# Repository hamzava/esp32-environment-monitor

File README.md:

# 🌱 ESP32 Environment Monitoring System
### Using ESP32 + ESP-IDF + I2C Sensors

🟢 This project represents an exploration into embedded firmware architecture, multi layer hardware design, and communication protocol integration using the ESP32 platform and the ESP-IDF framework.

## ◆ Project Overview

🟥 This project is a Environment Monitor prototype built using:

 - ESP-32 & ESP-IDF
 - BME280 Atmosphere Sensor
 - LTR390 UV Sensor

🟥 The objective was to to acquire environmental data from digital sensors and prepare it for network-based transmission.

This prototype is focused on:

✔ Multi-layer PCB & hardware design  </br>
✔ ESP-IDF firmware development </br>
✔ Peripheral communication via I2C </br>
✔ Power supply and regulation </br>

## ◆ Current Status:
- Fully operational Embedded System from working 4 layer PCB to a running ESP-IDF Super Loop

## ◆ Project Aims & Development Roadmap <br />
- This project was structured around incremental, demonstrable milestones, rather than a single monolithic goal.

## ✅ Completed / Implemented: 
🟢 Completely Functional 4-Layer PCB <br />
🟢 A running ESP-IDF based super loop <br />

## 🚧 In Progress / Planned Enhancements
🟡 Migration to FreeRTOS-Based Architecture <br />
🟡 WiFi Integration & MQTT Communication <br />

## ◆ Repository Structure
/Docs
 ├── Datasheets

/Hardware
 ├── Gerbers
 ├── Project_Media
 ├── Schematic & PCB

 /Firmware

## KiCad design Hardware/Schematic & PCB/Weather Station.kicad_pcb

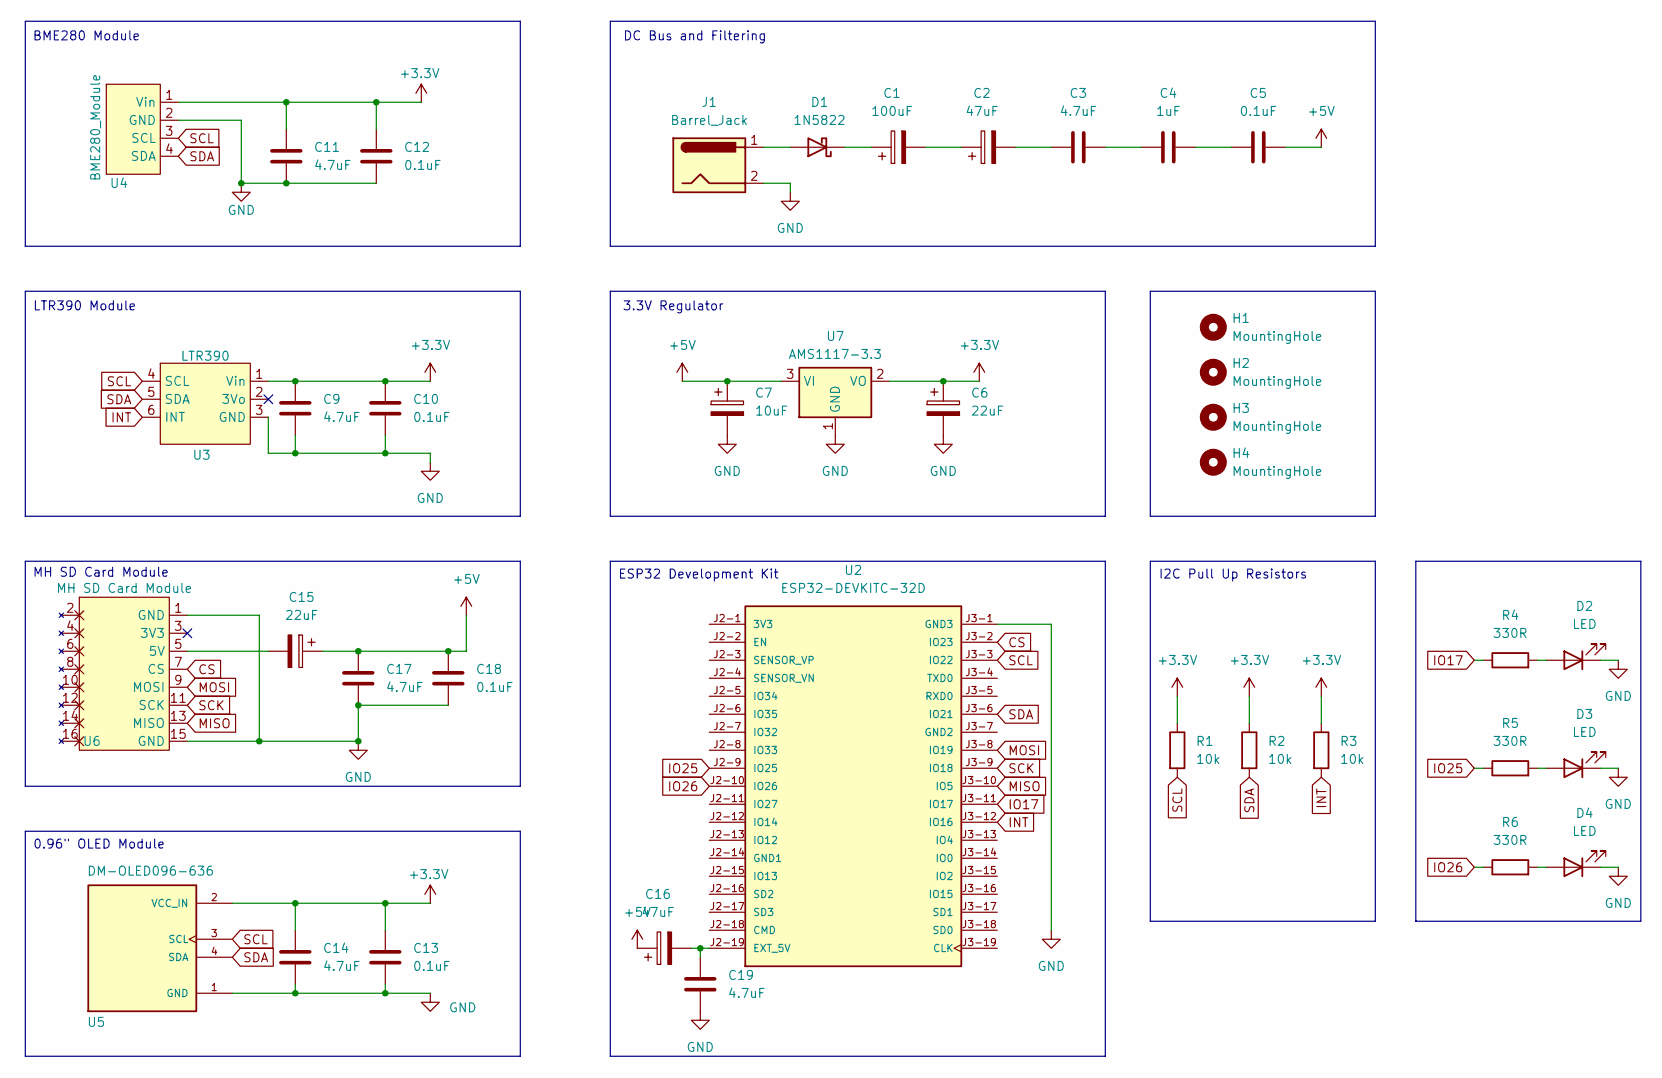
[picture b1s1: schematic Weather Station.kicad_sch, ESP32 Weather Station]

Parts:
C1: 100uF; CP_Radial_D5.0mm_P2.00mm
C2, C16: 47uF; CP_Radial_D5.0mm_P2.00mm
C3, C9, C11, C14, C17, C19: 4.7uF; C_0805_2012Metric_Pad1.18x1.45mm_HandSolder
C4: 1uF; C_0805_2012Metric_Pad1.18x1.45mm_HandSolder
C5, C10, C12, C13, C18: 0.1uF; C_0805_2012Metric_Pad1.18x1.45mm_HandSolder
C6: 22uF; CP_EIA-6032-28_Kemet-C_HandSolder
C7: 10uF; CP_EIA-6032-28_Kemet-C_HandSolder
C15: 22uF; CP_Radial_D5.0mm_P2.00mm
D1: 1N5822; SS34
D2, D3, D4: LED; LED_1206_3216Metric_Pad1.42x1.75mm_HandSolder
H1, H2, H3, H4: MountingHole; MountingHole_3.2mm_M3
J1: Barrel_Jack; BarrelJack_Wuerth_6941xx301002
R1, R2, R3: 10k; R_0805_2012Metric_Pad1.20x1.40mm_HandSolder
R4, R5, R6: 330R; R_0805_2012Metric_Pad1.20x1.40mm_HandSolder
U2: ESP32-DEVKITC-32D; PARTREV V4
U3: LTR390
U4: BME280_Module; BME 280 Module
U5: DM-OLED096-636; MODULE_DM-OLED096-636; PARTREV 2018-09-10
U6: MH SD Card Module; MH-SD_Card Module
U7: AMS1117-3.3; SOT-223-3_TabPin2

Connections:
+3.3V: C6.1, C9.2, C10.2, C11.2, C12.2, C13.2, C14.2, R1.1, R2.1, R3.1, U3.1 (Vin), U4.1 (Vin), U5.2 (VCC_IN), U7.2 (VO)
+5V: C5.2, C7.1, C15.1, C16.1, C17.2, C18.2, U7.3 (VI)
CS: U2.J3-2 (IO23), U6.7 (CS)
GND: C6.2, C7.2, C9.1, C10.1, C11.1, C12.1, C13.1, C14.1, C17.1, C18.1, C19.1, D2.1 (K), D3.1 (K), D4.1 (K), J1.2, U2.J3-1 (GND3), U3.3 (GND), U4.2 (GND), U5.1 (GND), U6.1 (GND), U6.15 (GND), U7.1 (GND)
INT: R3.2, U2.J3-12 (IO16), U3.6 (INT)
IO17: R4.1, U2.J3-11 (IO17)
IO25: R5.1, U2.J2-9 (IO25)
IO26: R6.1, U2.J2-10 (IO26)
MISO: U2.J3-10 (IO5), U6.13 (MISO)
MOSI: U2.J3-8 (IO19), U6.9 (MOSI)
unnamed: C1.2, C2.1
unnamed: C2.2, C3.1
unnamed: C3.2, C4.1
unnamed: C4.2, C5.1
unnamed: D1.2 (A), J1.1
unnamed: C1.1, D1.1 (K)
unnamed: D2.2 (A), R4.2
unnamed: D3.2 (A), R5.2
unnamed: D4.2 (A), R6.2
unnamed: C16.2, C19.2, U2.J2-19 (EXT_5V)
unnamed: C15.2, U6.5 (5V)
SCK: U2.J3-9 (IO18), U6.11 (SCK)
SCL: R1.2, U2.J3-3 (IO22), U3.4 (SCL), U4.3 (SCL), U5.3 (SCL)
SDA: R2.2, U2.J3-6 (IO21), U3.5 (SDA), U4.4 (SDA), U5.4 (SDA)

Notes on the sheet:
I2C Pull Up Resistors
LTR390 Module
3.3V Regulator
BME280 Module
ESP32 Development Kit
DC Bus and Filtering
MH SD Card Module
0.96" OLED Module

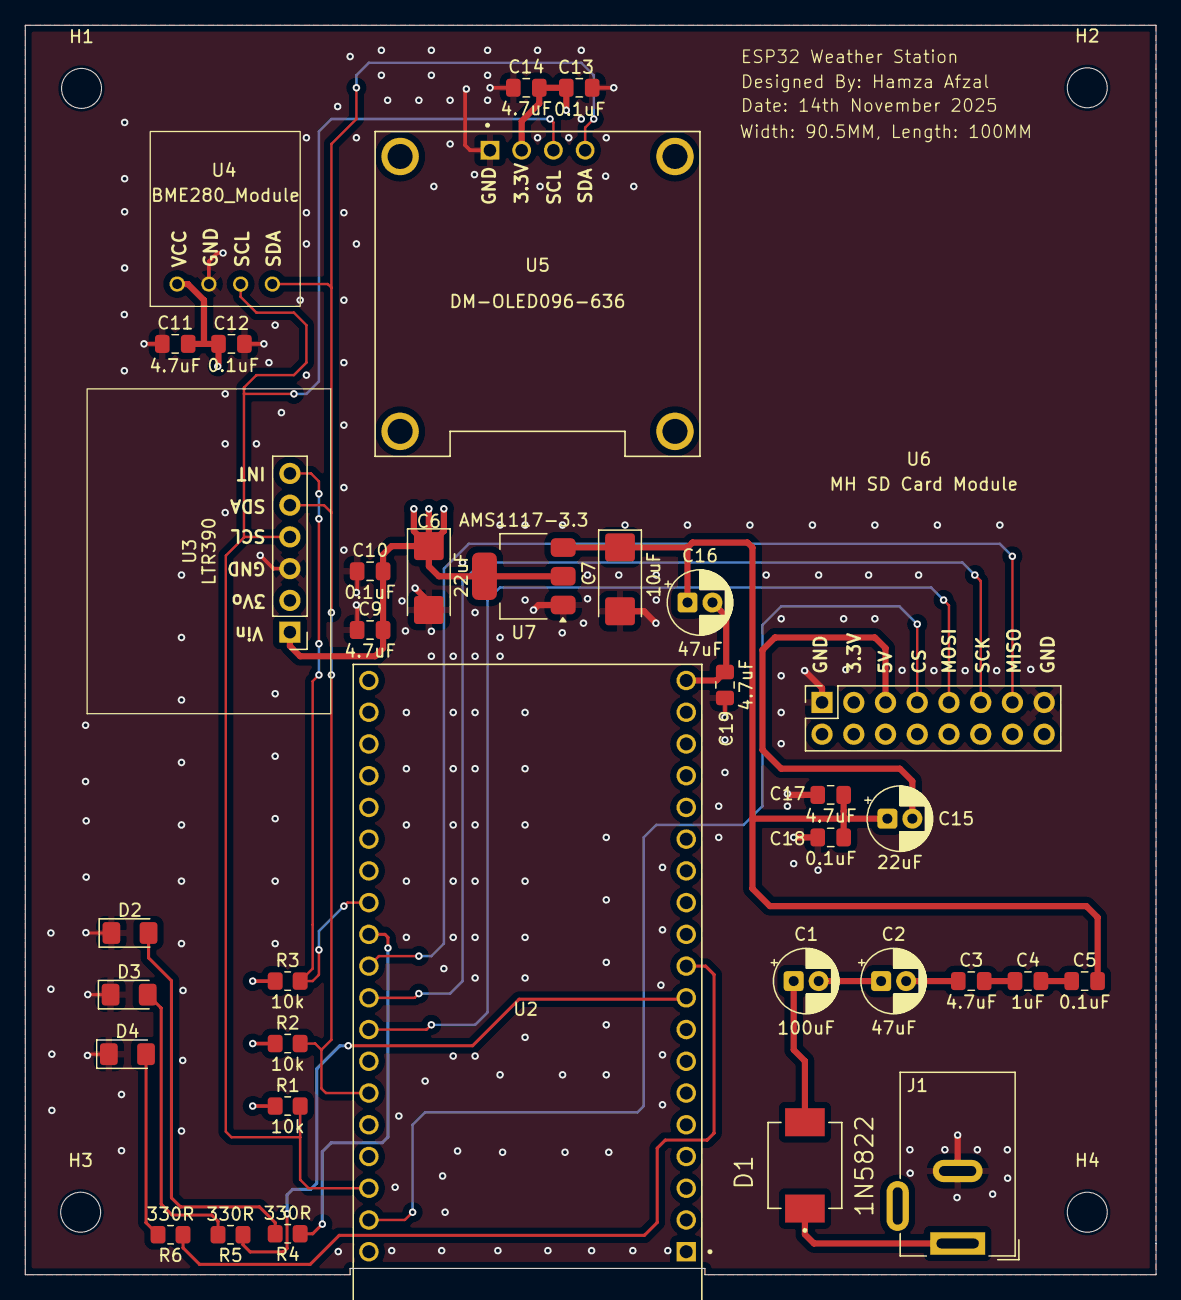
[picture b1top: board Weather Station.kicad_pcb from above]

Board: 4 copper layers, 90.5 x 100.0 mm, 39 parts (0 on the bottom side), 24 nets.

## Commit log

2026-02-24 Add ESP‑IDF firmware for environment monitor
